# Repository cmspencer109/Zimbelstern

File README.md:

# The St. Martin Luther Zimbelstern

A MIDI-enabled zimbelstern for organs without one.

<div style="display: flex; justify-content: space-between;">

</div>
<br>
This repo contains the code, schematics, and cad design files for the St. Martin Luther Zimbelstern.

## Design Overview

The St. Martin Luther Zimbelstern is an instrument designed for organs without a zimbelstern built into them. It features a solid oak case which fits comfortably on top of the organ console, allowing the controls to be in easy reach of the organist. In addition to a traditional Zimbel button for starting and stopping the zimbelstern, the St. Martin Luther Zimbelstern features a Prepare button which, when connected to a supported organ via MIDI, can identify when an organist begins playing the keyboards and automatically starts the zimbelstern.

Unlike more traditional designs which employ a rotating mechanism to strike a series of bells, this design allows for each bell to be played individually. Each bell is struck with a hammer which is actuated with an electromagnet. This allows the bells to be played at random, rather than in a predefined repeating sequence, as well as allowing adjustment over the speed and volume of the ringing. The electromagnets are controlled by a Raspberry Pi Pico microcontroller which lies at the heart of the zimbelstern, and is responsible for the entire operation of the zimbelstern.

The instrument uses 5 tuned Malmark handbells which form the D minor pentatonic scale. The pitches are D7, F7, G7, A7, and C8.

### MIDI Integration

The St. Martin Luther Zimbelstern has a MIDI IN port which can be connected to the MIDI OUT on a supported organ. The MIDI connection is only one-way, which means the zimbelstern only listens to the organ and does not talk back.

The MIDI connection is used for the Prepare button, which, when engaged will listen for "Note On" MIDI messages from the organ. When one of these messages is received, the microcontroller knows the organist has begun playing and will automatically start the zimbelstern.

Additionally, the MIDI connection is used to determine if any stops are engaged on the organ. This way, if the organist has pressed the Prepare button on the zimbelstern, but not yet engaged a registration on the organ, the zimbelstern will not start from an accidental silent key press. This functionality reads System Exclusive MIDI messages to identify if any stops are activated*, however, these are unique per organ manufacturer. As a result, the Prepare button will only work on Rodgers organs or any organ that uses the Rodgers/Roland SysEx message format. Support for other organs can be added by adding logic to read their SysEx message format.

*If the zimbelstern is plugged in after the organ is turned on, a stop change needs to be made on the organ to trigger a SysEx message so the zimbelstern can know the current state of the organ.

## Electronics

### Circuit Board

* [JLCPCB](https://jlcpcb.com/) was used to order the PCB. The folder `Zimbel-2024-03-03` contains a KiCad export of all the files needed to order a new board from a PCB fabricator.

## Meaning Behind the Name

The name "St. Martin Luther Zimbelstern" reflects several key points about this zimbelstern. It is named after the great reformer Martin Luther who is remembered as we celebrate various 500-year anniversaries of Luther's work during the time of the reformation. Second, since the sound of the zimbelstern often signifies the song of heaven, the additional title of "St." reminds us that we are joined with Martin Luther and all those who are saints in heaven by Jesus' blood. Third, this zimbelstern was designed and built specifically for Martin Luther Church in Sunset Hills, Missouri whose name is also reflected in this name.

## Known Design Flaws

This zimbelstern was developed rapidly over 6 months and has some flaws. Below is a list of things that should be improved in future versions:

* Hammers produce an undesirable clacking sound when striking the bell
  * This is caused by a number of reasons, and may not be fixable without changing the hammer mechanism entirely.
  * The clearest bell rings occur when the striking object makes contact for the shortest amount of time possible. The longer the striking object remains on the bell, the more muted the tone will become until it doesn't ring at all. This is the first issue. The electromagnets cannot move the hammers fast enough. One solution is to reduce the weight of the hammers so they can swing faster. A better solution would be to use a mechanism similar to a grandfather clock, where the hammer is pulled back and springs forward to strike the bell.
  * The second issue is that the wooden hammer is absorbing some of the vibrations when striking and the wood is producing a dull echoing sound. Loosening the brass hammer head and adding a felt pad between the wooden hammer has helped to reduce this, but does not solve it entirely. One solution is to build the hammers out of a different material, such as all brass.
* ZIMBEL piston lamp voltage not properly regulated
  * The piston lamps operate at 5v, and are said to be used with a series resistor in Rodgers organs. This same type of series resistor configuration was used in the zimbelstern circuit to reduce the main 12v source to 5v. However, since the electromagnets also draw from the main 12v source a flickering in the piston lamp is produced when the zimbelstern is ringing.
  * One solution is to properly regulate the 12v to 5v using a buck converter. In the production model, the series resistor was removed and an extra buck converter wired in place. A proper fix would build this into the PCB.

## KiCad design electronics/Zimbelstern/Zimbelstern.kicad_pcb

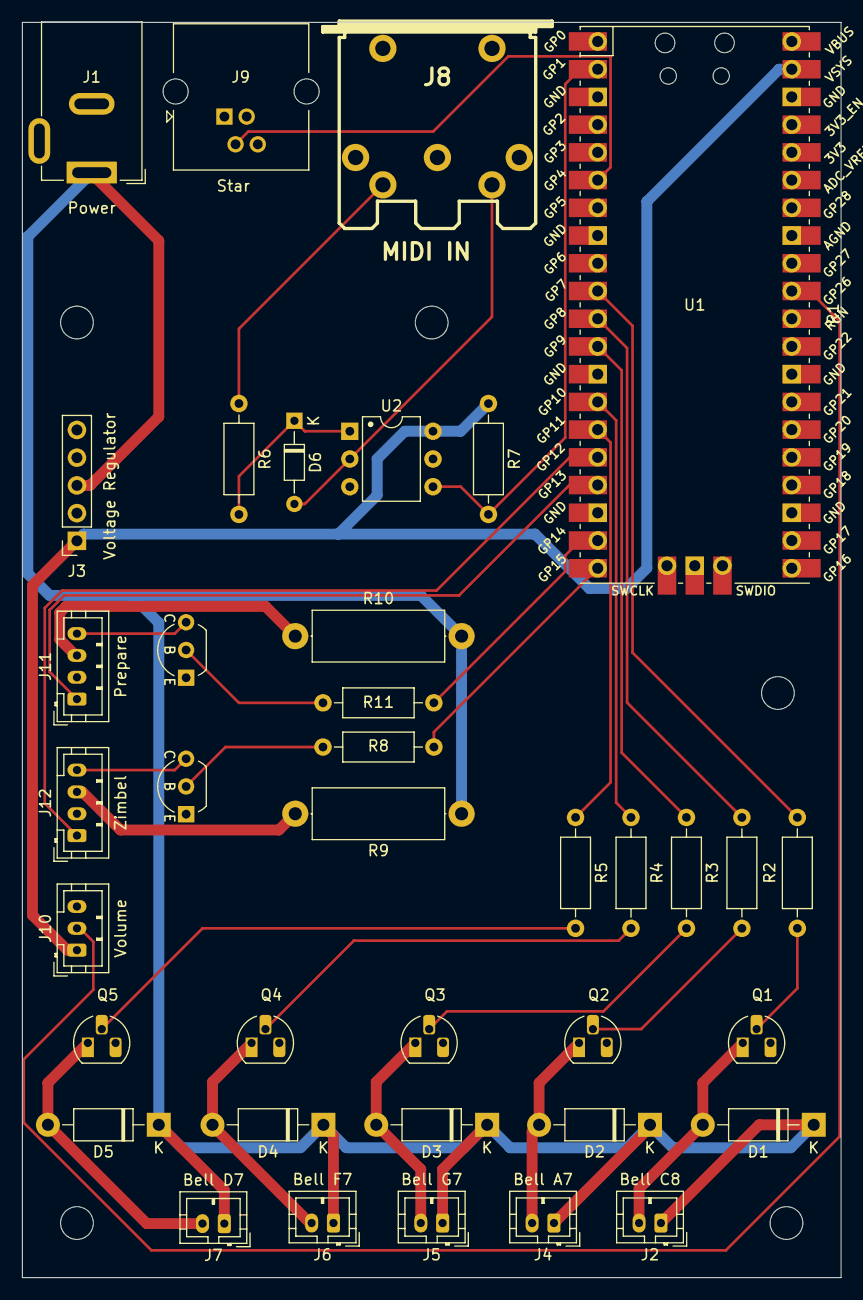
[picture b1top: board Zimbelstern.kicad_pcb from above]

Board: 2 copper layers, 75.0 x 115.0 mm, 43 parts (0 on the bottom side), 34 nets.

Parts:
D1, D2, D3, D4, D5: 1N4007; D_DO-41_SOD81_P10.16mm_Horizontal
D6: 1N914; D_DO-34_SOD68_P7.62mm_Horizontal
H1, H2, H3, H4, H5: MountingHole; MountingHole_3mm
J1: Power; BarrelJack_GCT_DCJ200-10-A_Horizontal
J2: Bell C8; JST_PH_B2B-PH-K_1x02_P2.00mm_Vertical
J3: Voltage Regulator; PinSocket_1x05_P2.54mm_Vertical
J4: Bell A7; JST_PH_B2B-PH-K_1x02_P2.00mm_Vertical
J5: Bell G7; JST_PH_B2B-PH-K_1x02_P2.00mm_Vertical
J6: Bell F7; JST_PH_B2B-PH-K_1x02_P2.00mm_Vertical
J7: Bell D7; JST_PH_B2B-PH-K_1x02_P2.00mm_Vertical
J8: MIDI IN; MIDI_DIN5
J9: Star; RJ14_Connfly_DS1133-S4_Horizontal
J10: Volume; JST_PH_B3B-PH-K_1x03_P2.00mm_Vertical
J11: Prepare; JST_PH_B4B-PH-K_1x04_P2.00mm_Vertical
J12: Zimbel; JST_PH_B4B-PH-K_1x04_P2.00mm_Vertical
Q1, Q2, Q3, Q4, Q5: Q_NPN_CBE; TO-92_HandSolder
Q6, Q7: 2N2222A-TO92; TO-92_Inline_Wide_EBC
R1, R2, R3, R4, R5: 510; R_Axial_DIN0207_L6.3mm_D2.5mm_P10.16mm_Horizontal
R6: 220; R_Axial_DIN0207_L6.3mm_D2.5mm_P10.16mm_Horizontal
R7: 470; R_Axial_DIN0207_L6.3mm_D2.5mm_P10.16mm_Horizontal
R8, R11: 1k; R_Axial_DIN0207_L6.3mm_D2.5mm_P10.16mm_Horizontal
R9, R10: 120; R_Axial_DIN0414_L11.9mm_D4.5mm_P15.24mm_Horizontal
U1: Pico; RPi_Pico_SMD_TH
U2: H11L1; DIP-6_W7.62mm

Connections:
+3V3: J3.1, J10.1, R7.1, U1.39 (VSYS), U2.6
+12V: D1.1 (K), D2.1 (K), D3.1 (K), D4.1 (K), D5.1 (K), J1.1, J2.1, J3.3, J4.1, J5.1, J6.1, J7.1, R9.1, R10.1
BELL1: R1.1, U1.10 (GPIO7)
BELL2: R2.1, U1.11 (GPIO8)
BELL3: R3.1, U1.12 (GPIO9)
BELL4: R4.1, U1.14 (GPIO10)
BELL5: R5.1, U1.15 (GPIO11)
GND: J1.2, J3.2, J9.1, J10.3, J11.2, J12.2, Q1.3 (E), Q2.3 (E), Q3.3 (E), Q4.3 (E), Q5.3 (E), Q6.1 (E), Q7.1 (E), U1.3 (GND), U1.8 (GND), U1.13 (GND), U1.18 (GND), U1.23 (GND), U1.28 (GND), U1.38 (GND), U1.42 (GND), U2.5
MIDI_RX: R7.2, U1.2 (GPIO1), U2.4
unnamed: D1.2 (A), J2.2, Q1.1 (C)
unnamed: D2.2 (A), J4.2, Q2.1 (C)
unnamed: D3.2 (A), J5.2, Q3.1 (C)
unnamed: D4.2 (A), J6.2, Q4.1 (C)
unnamed: D5.2 (A), J7.2, Q5.1 (C)
unnamed: D6.2 (A), J8.5, U2.2
unnamed: D6.1 (K), R6.2, U2.1
unnamed: J8.4, R6.1
unnamed: J11.3, R10.2
unnamed: J11.4, Q7.3 (C)
unnamed: J12.3, R9.2
unnamed: J12.4, Q6.3 (C)
unnamed: Q1.2 (B), R1.2
unnamed: Q2.2 (B), R2.2
unnamed: Q3.2 (B), R3.2
unnamed: Q4.2 (B), R4.2
unnamed: Q5.2 (B), R5.2
unnamed: Q6.2 (B), R8.2
unnamed: Q7.2 (B), R11.2
PREPARE_LAMP: R11.1, U1.19 (GPIO14)
PREPARE_SWITCH: J11.1, U1.17 (GPIO13)
STAR_TX: J9.2, U1.6 (GPIO4)
VOLUME_POT: J10.2, U1.31 (GPIO26_ADC0)
ZIMBLE_LAMP: R8.1, U1.20 (GPIO15)
ZIMBLE_SWITCH: J12.1, U1.16 (GPIO12)

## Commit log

2024-01-05 Removing files
2024-01-06 Fix midi trigger messages by excluding status byte
2024-01-07 Recorded midi data
2024-01-10 Remove unused programs
2024-01-10 Add support for ready button
2024-01-10 WIP: better midi implementation for rodgers sysex
2024-01-17 Update pins
2024-01-17 Fix zimbel ready feature to work with all types of note on off commands
2024-01-17 Pulsing electromagnet test
2024-01-17 Describe binding and activating process
2024-01-18 Updating midi data
2024-01-18 Proof of concept for binding to sysex
2024-01-18 Update py midi
2024-01-18 Update midi reader and add midi sender for testing
2024-01-23 Changes during organ test
2024-01-23 Add constants for times
2024-01-25 Fix writing midi trigger bytes to file
2024-01-28 Add stops_on handling
2024-01-31 Update magnet test code for new circuit
2024-01-31 Remove outdated zimbel async code that didnt have ready/prepare feature
2024-01-31 Renaming variables, cleaning/refactoring code
2024-02-01 wip: adding support for program change midi messages
2024-02-01 Integrate adjustment dials and code for triggering magnet
2024-02-08 Add stepper test
2024-02-11 Add star uart communication
2024-02-12 Star stepper motor tests
2024-02-12 Nice smooth acceleration and deceleration no jerks
2024-02-13 remove files and add test
2024-02-16 Fix/Add working magnet loop to main zimbel program
2024-02-22 Remove unused files
2024-02-22 Add arduino code for star
2024-02-22 Update to stream star bytes in a loop every 100 ms
2024-02-22 Adding constants for pins
2024-02-22 Renaming variables and adding bell note loop
2024-03-15 Pin updates, fix star loop
2024-03-16 Add bell loop task
2024-03-16 Add TODOs to work on
2024-03-21 Bell sequences for testing
2024-03-21 Star test conditional and print statements for testing
2024-03-21 Simplify bell sequence
2024-03-21 Convert to using tempo
2024-03-21 Organize and document variables
2024-03-21 Rename vars
2024-03-21 Rename name in readme
2024-03-24 Add random melody, and better separation for note playing functions
2024-03-25 Update midi activation implementation, wip on speed control, add easter egg
2024-03-25 tweak how tempo is used in note player
2024-03-26 Change zimbel toggle to work on button release
    Fixes zimbel starting to play when holding down zimbel button to enter program mode
2024-03-27 Move general cancel to be the last thing that gets handled when processing a midi message in zimbel mode
2024-03-27 Add support for organ power on midi message (used for clearing midi trigger)
2024-03-28 Add micro pico VScode plugin configuration
2024-03-28 set stops to off with gc piston
2024-03-29 Add comment to fix
2024-03-29 Tweak values
2024-03-30 Changes and fixes from organ testing on Good Friday
2024-03-30 Ignore micropico plugin and vs code config files
2024-03-30 Cleanup comments that were fixed and remove WIP code for volume fader
2024-03-30 Remove the option to allow repeats in random melody
2024-03-30 Tweak zimbel hold time values
2024-03-30 Format of print messages
2024-03-30 Rename for board
2024-03-30 Fix bug where any possible midi trigger would activate the zimbelstern if it was unset
2024-03-30 Decide best tempo
2024-03-31 Cleanup
2024-04-05 Fix syntax error
2024-04-06 Reduce max volume, fix playing a note to not cancel activation mode, and increase star data rate
2024-04-06 Disable pico led used for testing
2024-04-06 Implement random weighted note picker
    Also modify old traditional random note picker to be better and use same data structure as the weighted version
2024-04-06 Disable loading midi trigger from file for now
2024-04-06 Rename function for clarity
2024-04-06 Add logging
2024-04-06 Add zimbel stats processer
2024-04-13 Better design for overriding tempo and volume in note player
2024-04-13 Refactor volume and bell strike functions
2024-04-13 Increase tempo, make random note picker replay same note less frequently
2024-04-13 Reduce tempo
2024-04-13 Optional melodies
2024-04-14 Revert tempo
2024-04-14 Add support for fading in volume and tempo
2024-04-16 Add digital bell player for at-home testing
2024-06-02 Update digital bells, add logic for trigger type
2024-06-02 WIP: removing digital bell player and midi trigger functionality
2024-06-02 WIP: continue refactoring and removing unused code
2024-06-03 WIP: continue refactoring and add hymn player
2024-06-03 Change zimbel piston to start on press instead of release
2024-06-06 Updates to melody and hymn player
2024-06-07 Decide settings to use in production
2024-06-07 Add star code and photos of zimbelstern
2024-06-07 Adding kicad and fusion 360 files
2024-06-10 Updates to readme
2025-04-18 Add 1 second volume fade at start
